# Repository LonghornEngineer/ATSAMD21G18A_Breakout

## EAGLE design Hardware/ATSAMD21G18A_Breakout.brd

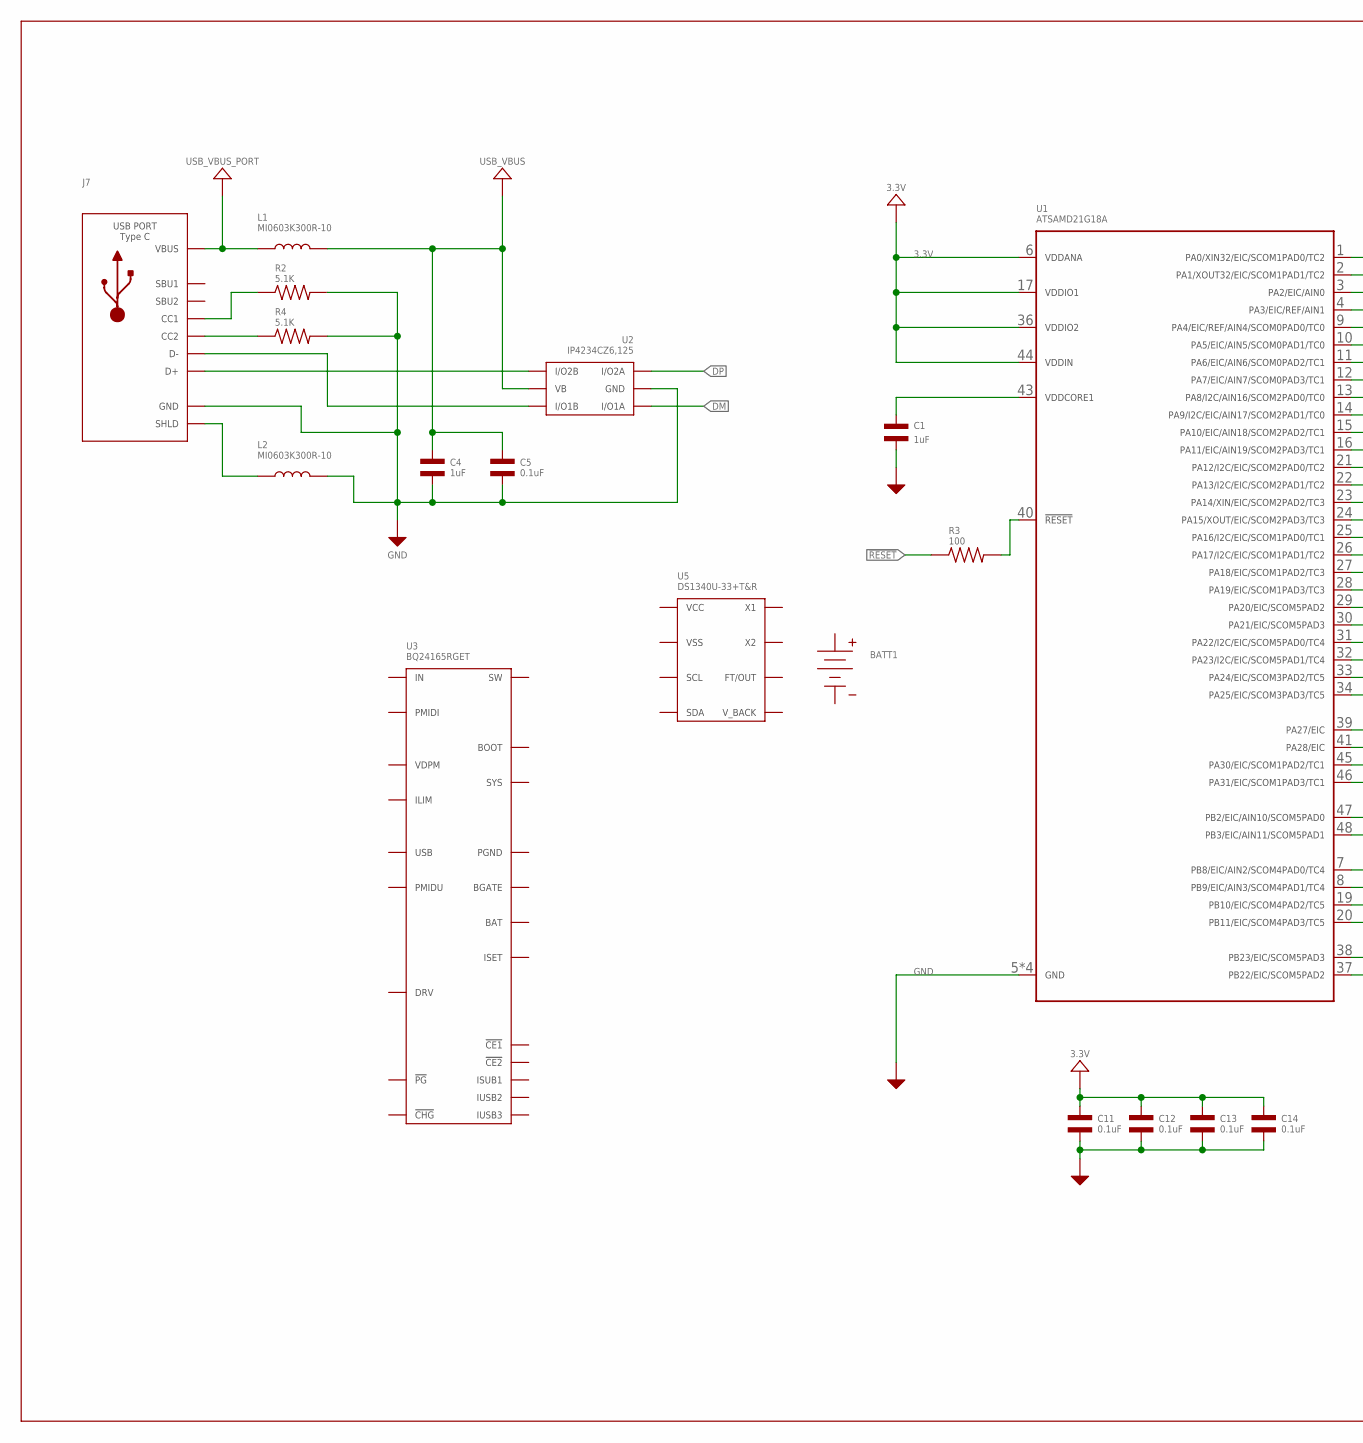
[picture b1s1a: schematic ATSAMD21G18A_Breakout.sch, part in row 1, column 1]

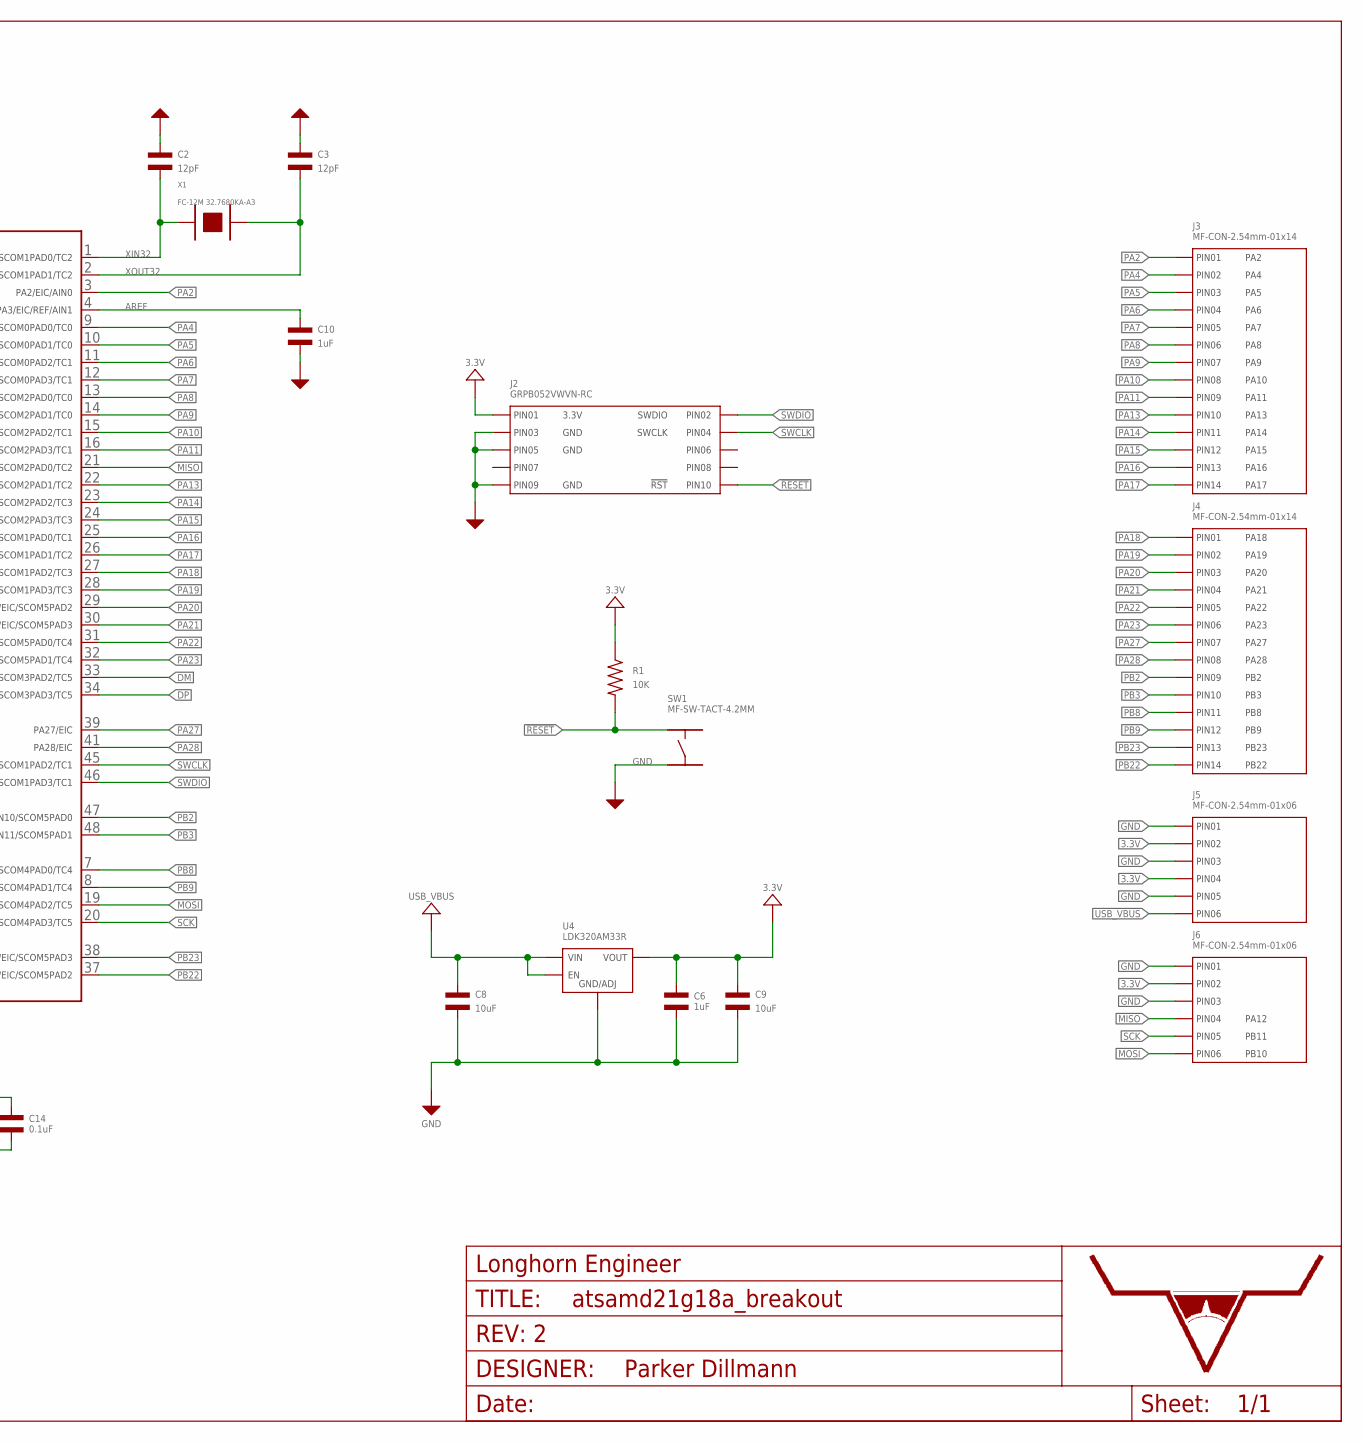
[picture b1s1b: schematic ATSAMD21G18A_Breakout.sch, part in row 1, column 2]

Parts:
BATT1: BATTERY_KEYSTONE_1074; 1074
C1, C4, C10: 1uF; C0402; MPN MF-CAP-0603-1uF
C2, C3: 12pF; C0402; MPN CC0603JRNPO9BN120
C5, C11, C12, C13, C14: 0.1uF; C0402; MPN MF-CAP-0603-0.1uF
C6: 1uF; C0603; MPN MF-CAP-0603-1uF
C8, C9: 10uF; C1206; MPN MF-CAP-1206-10uF
J2: GRPB052VWVN-RC
J3, J4: MF-CON-2.54mm-01x14; PTH_2.54MM_01X14
J5, J6: MF-CON-2.54mm-01x06; PTH_2.54MM_01X06
J7: USB_TYPE-C_MINIMAL; TYPE-C-31-M-12
L1, L2: MI0603K300R-10; L0603; MPN MI0603K300R-10
R1: 10K; R0402; MPN MF-RES-0603-10K
R2, R4: 5.1K; R0402; MPN ERJ-3EKF5101V
R3: 100; R0402; MPN MF-RES-0603-100
SW1: MF-SW-TACT-4.2MM; TACT4.2MM
U1: ATSAMD21G18A; ATSAMD21G18A_TQFP-48; MPN ATSAMD21G18A-AU
U2: IP4234CZ6,125; IP4234CZ6_SOT-457-6; MPN IP4234CZ6,125
U3: BQ24165RGET; BQ24165_QFN-24
U4: LDK320AM33R; SOT-23-5; MPN LDK320AM33R
U5: DS1340U-33+T&R; DS1340Z_USOP; MPN DS1340U-33+T&R
U$8: LHE_FRAME
X1: FC-12M 32.7680KA-A3; FC-12M; MPN FC-12M 32.7680KA-A3

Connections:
3.3V: C6.P$1, C9.P$1, C11.P$1, C12.P$1, C13.P$1, C14.P$1, J2.1 (PIN1), J5.P$2 (PIN2), J5.P$4 (PIN4), J6.P$2 (PIN2), R1.P$1, U1.6 (VDDANA), U1.17 (VDDIO1), U1.36 (VDDIO2), U1.44 (VDDIN), U4.P$5 (VOUT)
!RESET: J2.10 (PIN10), R1.P$2, R3.P$1, SW1.P$1
AREF: C10.P$1, U1.4 (PA3/EIC/REF/AIN1)
D+: J7.A6 (D+), J7.B6 (D+), U2.4 (I/O2B)
D-: J7.A7 (D-), J7.B7 (D-), U2.3 (I/O1B)
DM: U1.33 (PA24/EIC/SCOM3PAD2/TC5), U2.1 (I/O1A)
DP: U1.34 (PA25/EIC/SCOM3PAD3/TC5), U2.6 (I/O2A)
GND: C1.P$2, C2.P$1, C3.P$1, C4.P$2, C5.P$2, C6.P$2, C8.P$2, C9.P$2, C10.P$2, C11.P$2, C12.P$2, C13.P$2, C14.P$2, J2.3 (PIN3), J2.5 (PIN5), J2.9 (PIN9), J5.P$1 (PIN1), J5.P$3 (PIN3), J5.P$5 (PIN5), J6.P$1 (PIN1), J6.P$3 (PIN3), J7.A1/B12 (GND), J7.B1/A12 (GND), L2.P$2, R2.P$2, R4.P$2, SW1.P$3, U1.5 (GND), U1.18 (GND), U1.35 (GND), U1.42 (GND), U2.2 (GND), U4.P$2 (GND/ADJ)
MISO: J6.P$4 (PIN4), U1.21 (PA12/I2C/EIC/SCOM2PAD0/TC2)
MOSI: J6.P$6 (PIN6), U1.19 (PB10/EIC/SCOM4PAD2/TC5)
unnamed: J7.A5 (CC1), R2.P$1
unnamed: J7.B5 (CC2), R4.P$1
PA2: J3.P$1 (PIN1), U1.3 (PA2/EIC/AIN0)
PA4: J3.P$2 (PIN2), U1.9 (PA4/EIC/REF/AIN4/SCOM0PAD0/TC0)
PA5: J3.P$3 (PIN3), U1.10 (PA5/EIC/AIN5/SCOM0PAD1/TC0)
PA6: J3.P$4 (PIN4), U1.11 (PA6/EIC/AIN6/SCOM0PAD2/TC1)
PA7: J3.P$5 (PIN5), U1.12 (PA7/EIC/AIN7/SCOM0PAD3/TC1)
PA8: J3.P$6 (PIN6), U1.13 (PA8/I2C/AIN16/SCOM2PAD0/TC0)
PA9: J3.P$7 (PIN7), U1.14 (PA9/I2C/EIC/AIN17/SCOM2PAD1/TC0)
PA10: J3.P$8 (PIN8), U1.15 (PA10/EIC/AIN18/SCOM2PAD2/TC1)
PA11: J3.P$9 (PIN9), U1.16 (PA11/EIC/AIN19/SCOM2PAD3/TC1)
PA13: J3.P$10 (PIN10), U1.22 (PA13/I2C/EIC/SCOM2PAD1/TC2)
PA14: J3.P$11 (PIN11), U1.23 (PA14/XIN/EIC/SCOM2PAD2/TC3)
PA15: J3.P$12 (PIN12), U1.24 (PA15/XOUT/EIC/SCOM2PAD3/TC3)
PA16: J3.P$13 (PIN13), U1.25 (PA16/I2C/EIC/SCOM1PAD0/TC1)
PA17: J3.P$14 (PIN14), U1.26 (PA17/I2C/EIC/SCOM1PAD1/TC2)
PA18: J4.P$1 (PIN1), U1.27 (PA18/EIC/SCOM1PAD2/TC3)
PA19: J4.P$2 (PIN2), U1.28 (PA19/EIC/SCOM1PAD3/TC3)
PA20: J4.P$3 (PIN3), U1.29 (PA20/EIC/SCOM5PAD2)
PA21: J4.P$4 (PIN4), U1.30 (PA21/EIC/SCOM5PAD3)
PA22: J4.P$5 (PIN5), U1.31 (PA22/I2C/EIC/SCOM5PAD0/TC4)
PA23: J4.P$6 (PIN6), U1.32 (PA23/I2C/EIC/SCOM5PAD1/TC4)
PA27: J4.P$7 (PIN7), U1.39 (PA27/EIC)
PA28: J4.P$8 (PIN8), U1.41 (PA28/EIC)
PB2: J4.P$9 (PIN9), U1.47 (PB2/EIC/AIN10/SCOM5PAD0)
PB3: J4.P$10 (PIN10), U1.48 (PB3/EIC/AIN11/SCOM5PAD1)
PB8: J4.P$11 (PIN11), U1.7 (PB8/EIC/AIN2/SCOM4PAD0/TC4)
PB9: J4.P$12 (PIN12), U1.8 (PB9/EIC/AIN3/SCOM4PAD1/TC4)
PB22: J4.P$14 (PIN14), U1.37 (PB22/EIC/SCOM5PAD2)
PB23: J4.P$13 (PIN13), U1.38 (PB23/EIC/SCOM5PAD3)
RESETLIN: R3.P$2, U1.40 (!RESET)
SCK: J6.P$5 (PIN5), U1.20 (PB11/EIC/SCOM4PAD3/TC5)
SHEILD2: J7.MT_B_0 (SHLD), J7.MT_B_1 (SHLD), J7.MT_B_2 (SHLD), J7.MT_B_3 (SHLD), J7.MT_T_0 (SHLD), J7.MT_T_1 (SHLD), J7.MT_T_2 (SHLD), J7.MT_T_3 (SHLD), L2.P$1
SWCLK: J2.4 (PIN4), U1.45 (PA30/EIC/SCOM1PAD2/TC1)
SWDIO: J2.2 (PIN2), U1.46 (PA31/EIC/SCOM1PAD3/TC1)
USB_VBUS: C4.P$1, C5.P$1, C8.P$1, J5.P$6 (PIN6), L1.P$2, U2.5 (VB), U4.P$1 (VIN), U4.P$3 (EN)
USB_VBUS_PORT: J7.A4/B9 (VBUS), J7.B4/A9 (VBUS), L1.P$1
VDDCORE: C1.P$1, U1.43 (VDDCORE1)
XIN32: C2.P$2, U1.1 (PA0/XIN32/EIC/SCOM1PAD0/TC2), X1.P$1
XOUT32: C3.P$2, U1.2 (PA1/XOUT32/EIC/SCOM1PAD1/TC2), X1.P$2

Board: 4 copper layers, 34 parts (10 on the bottom side), 50 nets, no tracks yet.

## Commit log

2019-07-22 First Push. Moving over from Previous Repo.
2019-07-22 removed tag connect and added LDK320AM33R for the LDO

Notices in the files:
parts and their libraries:
PP_Aesthetics: (c) 2019 Longhorn Engineer
